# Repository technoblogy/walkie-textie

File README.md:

# Walkie-Textie Wireless Communicator
The Walkie-Textie is a simple handheld device with a 12-key keypad and OLED display that allows you to send and receive text messages using the LoRa wireless protocol.

For more information see <http://www.technoblogy.com/show?2AON>.

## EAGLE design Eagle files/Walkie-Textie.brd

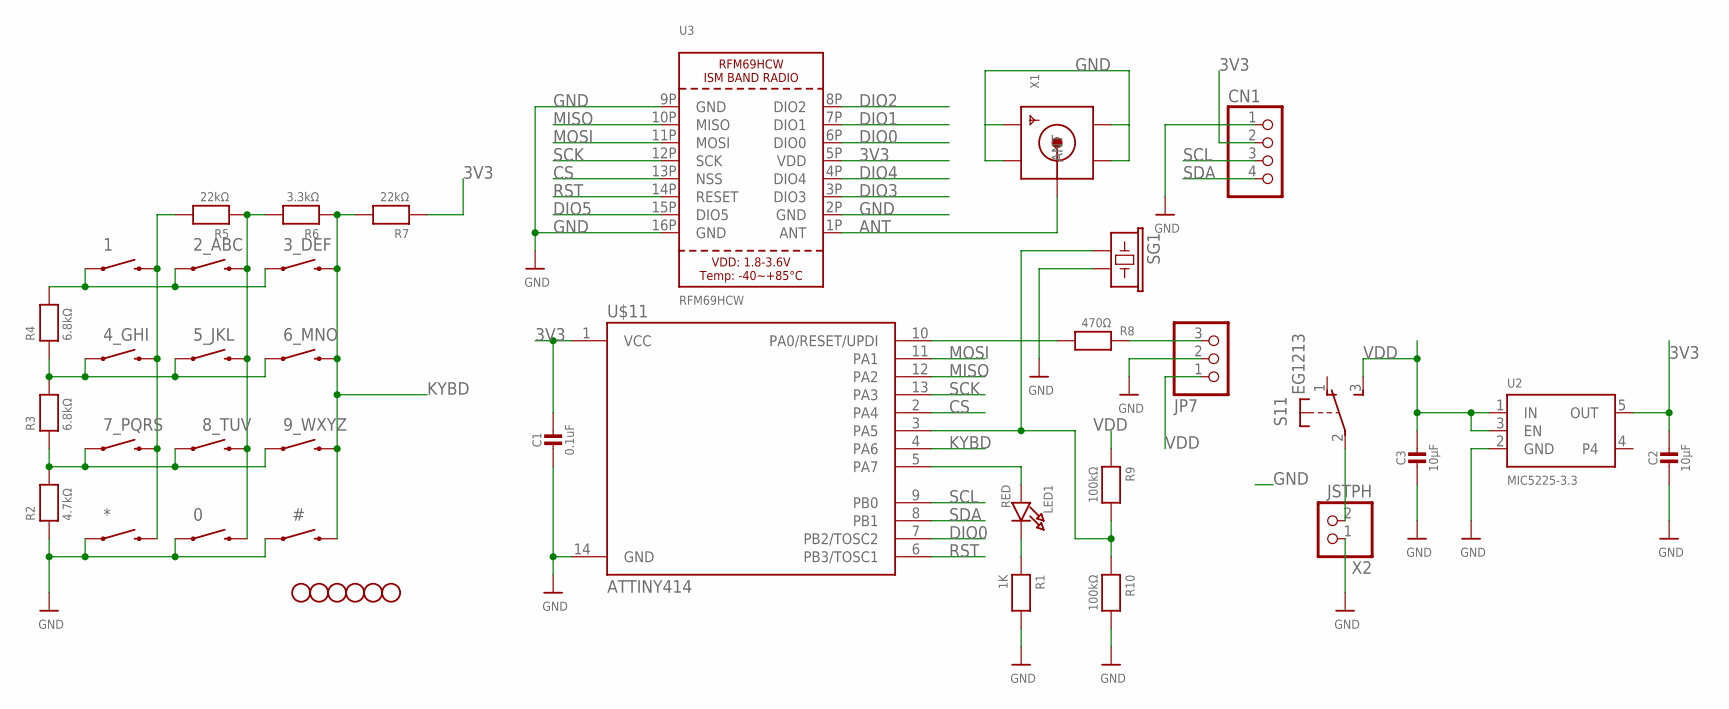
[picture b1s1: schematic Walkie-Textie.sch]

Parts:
0, 1, 2_ABC, 3_DEF, 4_GHI, 5_JKL, 6_MNO, 7_PQRS, 8_TUV, 9_WXYZ: SWITCH-MOMENTARY-2SMD-4; TACTILE_SWITCH_TALL
#: SWITCH-MOMENTARY-2SMD-4; TACTILE_SWITCH_TALL
*: SWITCH-MOMENTARY-2SMD-4; TACTILE_SWITCH_TALL
C1: 0.1uF; 0805-NO
C2, C3: 10µF; 0805-NO
CN1: HEADER-1X4ROUND; 1X04_ROUND
JP1, JP2, JP3, JP4, JP5, JP6: STAND-OFF
JP7: PINHD-1X3CB; 1X03-CLEANBIG
LED1: RED; CHIPLED_0805_NOOUTLINE
R1: 1K; _0805MP
R2: 4.7kΩ; _0805MP
R3, R4: 6.8kΩ; _0805MP
R5, R7: 22kΩ; _0805MP
R6: 3.3kΩ; _0805MP
R8: 470Ω; _0805MP
R9, R10: 100kΩ; _0805MP
S1: EG1213
SG1: BUZZERSMD3; BUZZER-CMT1102
U2: MIC5225-3.3; SOT23-5
U3: RFM69HCW; RFMHCW_SMT
U$11: ATTINY414; SO14
X1: SMACONNECTOR_EDGE; SMA_EDGELAUNCH
X2: JSTPH; JSTPH2

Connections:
3V3: C1.1, C2.1, CN1.2, R7.1, U2.5 (OUT), U3.5P (VDD), U$11.1 (VCC)
ANT: U3.1P (ANT), X1.P (ANT)
CS: U3.13P (NSS), U$11.2 (PA4)
DIO0: U3.6P (DIO0), U$11.7 (PB2/TOSC2)
DIO1: U3.7P (DIO1)
DIO2: U3.8P (DIO2)
DIO3: U3.3P (DIO3)
DIO4: U3.4P (DIO4)
DIO5: U3.15P (DIO5)
GND: 0.A2 (1), #.A2 (1), *.A2 (1), C1.2, C2.2, C3.2, CN1.1, JP7.2, R1.2, R2.1, R10.2, SG1.2, U2.2 (GND), U3.2P (GND), U3.9P (GND), U3.16P (GND), U$11.14 (GND), X1.GND@1 (GND4), X1.GND@2 (GND3), X1.GND@3 (GND2), X1.GND@4 (GND1), X2.1
GND1: 1.A2 (1), 2_ABC.A2 (1), 3_DEF.A2 (1), R4.2
KYBD: 3_DEF.B2 (2), 6_MNO.B2 (2), 9_WXYZ.B2 (2), #.B2 (2), R6.1, R7.2, U$11.4 (PA6)
MISO: U3.10P (MISO), U$11.12 (PA2)
MOSI: U3.11P (MOSI), U$11.11 (PA1)
unnamed: R8.2, U$11.10 (PA0/RESET/UPDI)
unnamed: LED1.A, U$11.5 (PA7)
unnamed: JP7.3, R8.1
unnamed: 4_GHI.A2 (1), 5_JKL.A2 (1), 6_MNO.A2 (1), R3.2, R4.1
unnamed: 7_PQRS.A2 (1), 8_TUV.A2 (1), 9_WXYZ.A2 (1), R2.2, R3.1
unnamed: R9.2, R10.1, SG1.1, U$11.3 (PA5)
unnamed: 1.B2 (2), 4_GHI.B2 (2), 7_PQRS.B2 (2), *.B2 (2), R5.2
unnamed: 0.B2 (2), 2_ABC.B2 (2), 5_JKL.B2 (2), 8_TUV.B2 (2), R5.1, R6.2
unnamed: LED1.C, R1.1
unnamed: S1.2, X2.2
RST: U3.14P (RESET), U$11.6 (PB3/TOSC1)
SCK: U3.12P (SCK), U$11.13 (PA3)
SCL: CN1.3, U$11.9 (PB0)
SDA: CN1.4, U$11.8 (PB1)
VDD: C3.1, JP7.1, R9.1, S1.3 (S), U2.1 (IN), U2.3 (EN)

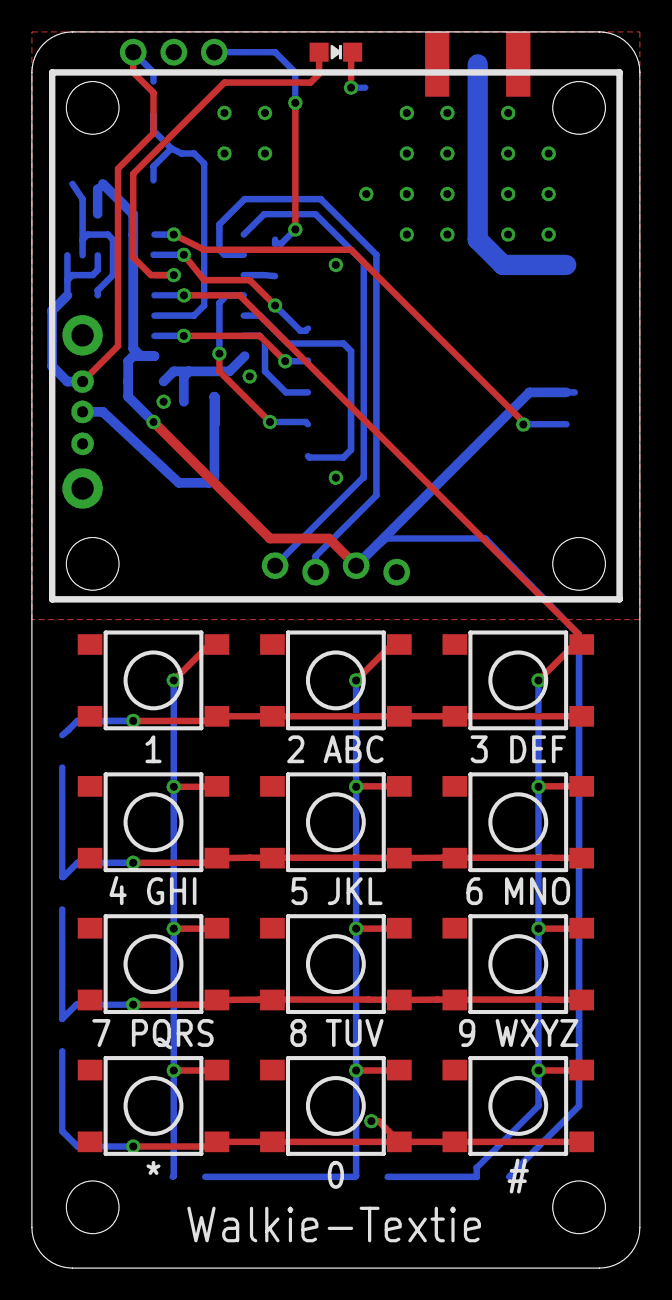
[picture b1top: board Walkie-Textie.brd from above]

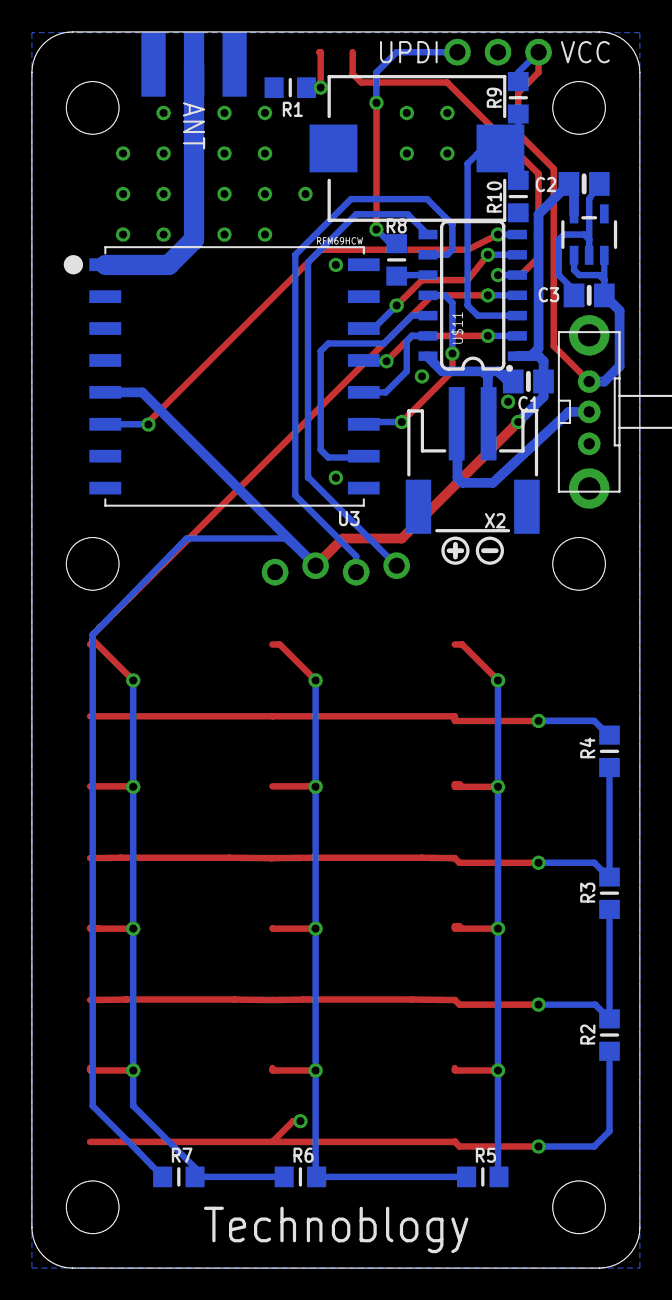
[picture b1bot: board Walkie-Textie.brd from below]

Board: 2 copper layers, 38.1 x 77.5 mm, 43 parts (22 on the bottom side), 24 nets.

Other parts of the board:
U$7: SYMBOL_PLUS
U$14: SYMBOL_MINUS

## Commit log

2025-07-29 Version 1 - 29th July 2025

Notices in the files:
parts and their libraries:
SparkFun-Electromechanical: Licensing: Creative Commons ShareAlike 4.0 International - https://creativecommons.org/licenses/by-sa/4.0
